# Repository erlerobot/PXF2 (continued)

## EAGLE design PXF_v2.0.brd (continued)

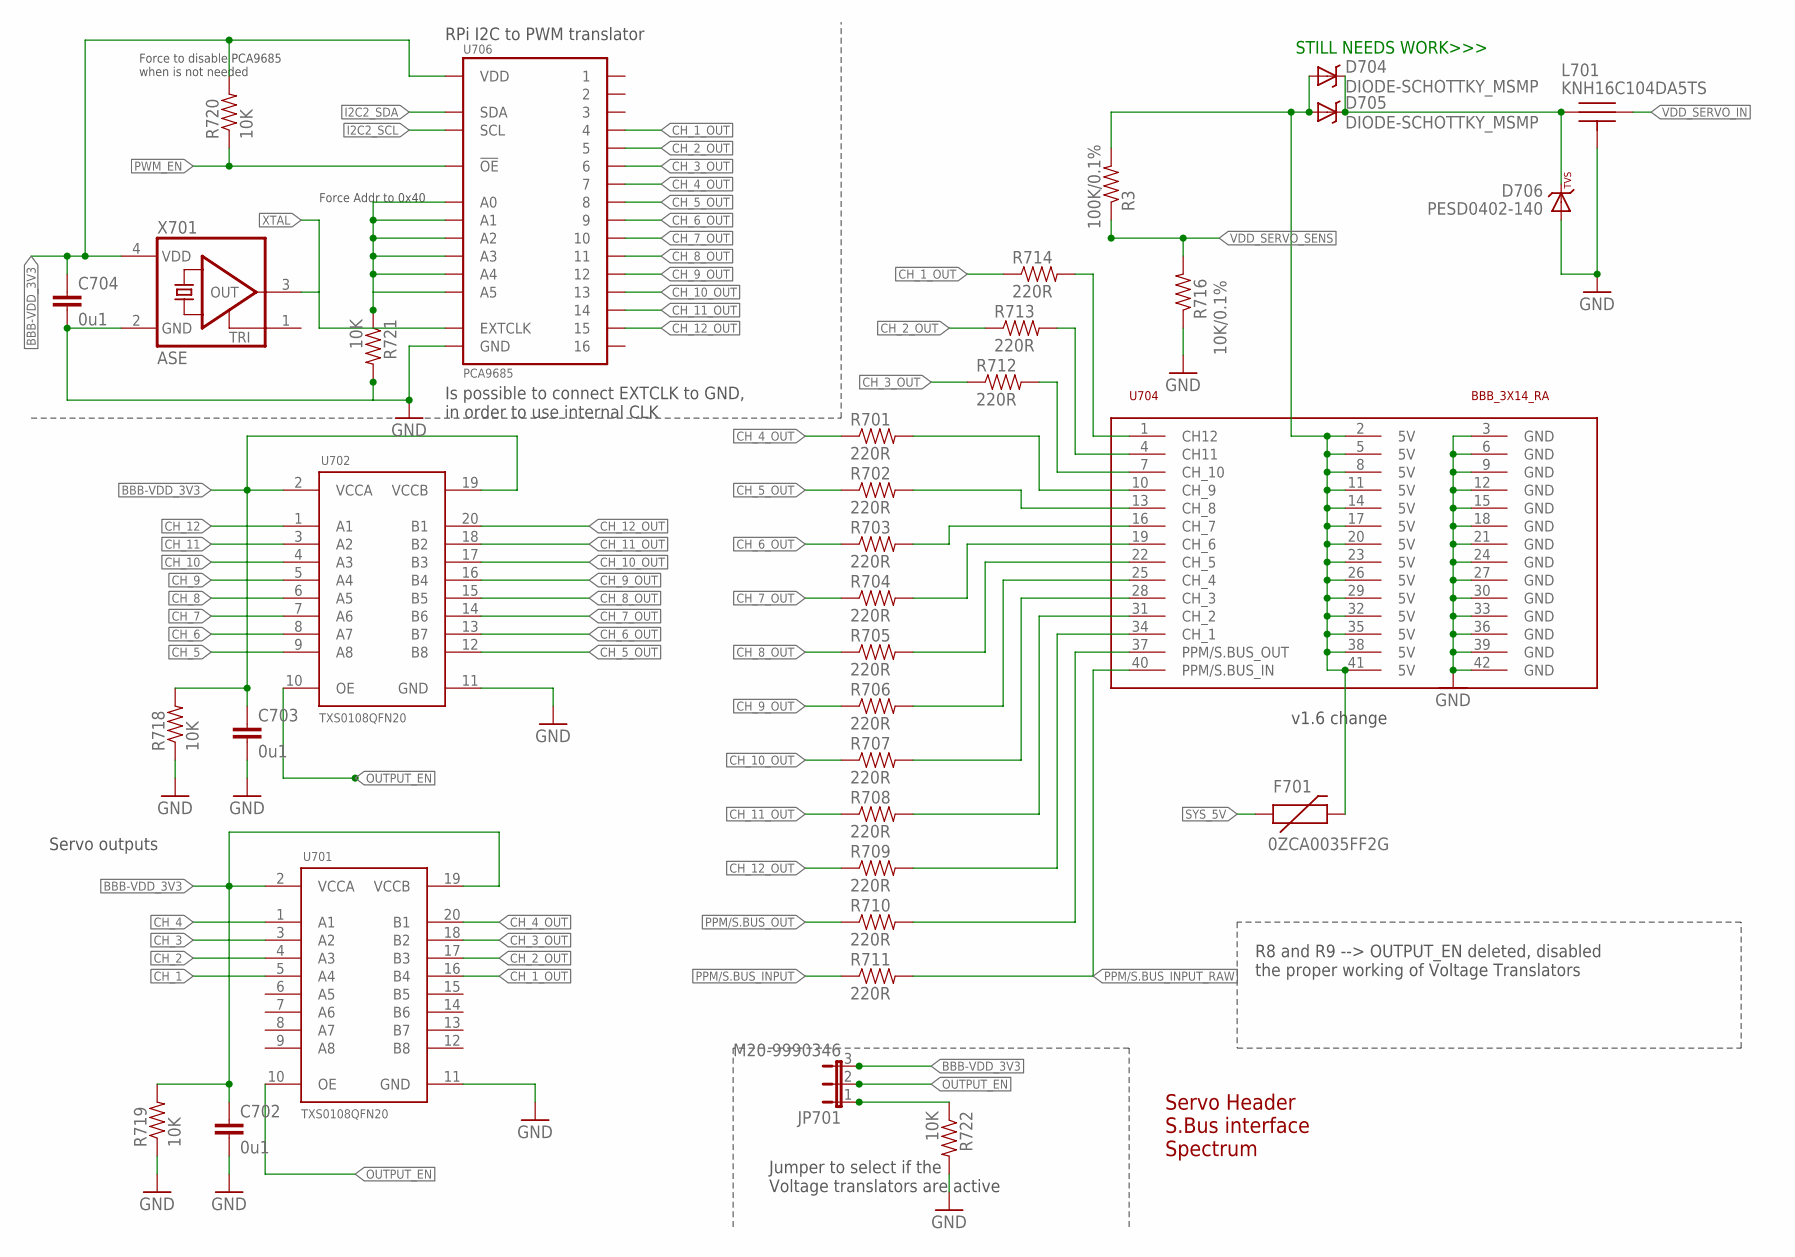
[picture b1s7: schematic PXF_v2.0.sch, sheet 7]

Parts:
C702, C703, C704: 0u1; 0402-CAP; PARTNO CC0402ZRY5V7BB104
D704, D705: DIODE-SCHOTTKY_MSMP; MICROSMP; PARTNO SS14
D706: PESD0402-140; 0402-TVS; PARTNO PESD0402-140
F701: 0ZCA0035FF2G; PTC-1206; PARTNO 0ZCA0035FF2G
JP701: M20-9990346; JP2
L701: KNH16C104DA5TS; KYOCERA-KNH16-DA; PARTNO KNH16C104DA5TS
R3: 100K/0.1%; 0402-RES; PARTNO ERA-2AEB104X
R701, R702, R703, R704, R705, R706, R707, R708, R709, R710, R711, R712, R713, R714: 220R; 0402-RES; PARTNO RC0402FR-07120RL
R716: 10K/0.1%; 0402-RES; PARTNO ERA-2AEB103X
R718, R719, R720, R721, R722: 10K; 0402-RES; PARTNO ERA-2AEB103X
U701, U702: TXS0108QFN20; QFN20-RGY; PARTNO TXS0108ERGYR
U704: BBB_3X14_RA; 3X14RA; PARTNO 07579
U706: PCA9685; HVQFN28
X701: ASE; MPN ASFL1-24.576MHZ-EC-T

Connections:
BBB-VDD_3V3: C702.P$1 (1), C703.P$1 (1), C704.P$1 (1), JP701.3, R718.P$2 (2), R719.P$2 (2), R720.P$2 (2), U701.2 (VCCA), U701.19 (VCCB), U702.2 (VCCA), U702.19 (VCCB), U706.25 (VDD), X701.4 (VDD); also elsewhere on the board
CH_1: U701.5 (A4); also elsewhere on the board
CH_1_OUT: R714.P$1 (1), U701.16 (B4), U706.6 (4)
CH_2: U701.4 (A3); also elsewhere on the board
CH_2_OUT: R713.P$1 (1), U701.17 (B3), U706.7 (5)
CH_3: U701.3 (A2); also elsewhere on the board
CH_3_OUT: R712.P$1 (1), U701.18 (B2), U706.8 (6)
CH_4: U701.1 (A1); also elsewhere on the board
CH_4_OUT: R701.P$1 (1), U701.20 (B1), U706.9 (7)
CH_5: U702.9 (A8); also elsewhere on the board
CH_5_OUT: R702.P$1 (1), U702.12 (B8), U706.10 (8)
CH_6: U702.8 (A7); also elsewhere on the board
CH_6_OUT: R703.P$1 (1), U702.13 (B7), U706.12 (9)
CH_7: U702.7 (A6); also elsewhere on the board
CH_7_OUT: R704.P$1 (1), U702.14 (B6), U706.13 (10)
CH_8: U702.6 (A5); also elsewhere on the board
CH_8_OUT: R705.P$1 (1), U702.15 (B5), U706.14 (11)
CH_9: U702.5 (A4); also elsewhere on the board
CH_9_OUT: R706.P$1 (1), U702.16 (B4), U706.15 (12)
CH_10: U702.4 (A3); also elsewhere on the board
CH_10_OUT: R707.P$1 (1), U702.17 (B3), U706.16 (13)
CH_11: U702.3 (A2); also elsewhere on the board
CH_11_OUT: R708.P$1 (1), U702.18 (B2), U706.17 (14)
CH_12: U702.1 (A1); also elsewhere on the board
CH_12_OUT: R709.P$1 (1), U702.20 (B1), U706.18 (15)
FMU-CH6-PROT: R708.P$2 (2), U704.31 (CH_2)
GND: C702.P$2 (2), C703.P$2 (2), C704.P$2 (2), D706.A, L701.P$3, L701.P$4, L701.P$5, R716.P$1 (1), R718.P$1 (1), R719.P$1 (1), R721.P$2 (2), R722.P$2 (2), U701.11 (GND), U702.11 (GND), U704.3 (GND), U704.6 (GND), U704.9 (GND), U704.12 (GND), U704.15 (GND), U704.18 (GND), U704.21 (GND), U704.24 (GND), U704.27 (GND), U704.30 (GND), U704.33 (GND), U704.36 (GND), U704.39 (GND), U704.42 (GND), U706.11 (GND), U706.PAD (GND), X701.2 (GND); also elsewhere on the board
I2C2_SCL: U706.23 (SCL); also elsewhere on the board
I2C2_SDA: U706.24 (SDA); also elsewhere on the board
IO-CH1-PROT: R707.P$2 (2), U704.28 (CH_3)
IO-CH8-PROT: R712.P$2 (2), U704.7 (CH_10)
unnamed: R721.P$1 (1), U706.1 (A3), U706.2 (A4), U706.21 (A5), U706.26 (A0), U706.27 (A1), U706.28 (A2)
unnamed: D704.CATHODE (C), D705.CATHODE (C), D706.C, L701.P$1
unnamed: JP701.1, R722.P$1 (1)
unnamed: D704.ANODE (A), D705.ANODE (A), F701.2, R3.P$2 (2), U704.2 (5V), U704.5 (5V), U704.8 (5V), U704.11 (5V), U704.14 (5V), U704.17 (5V), U704.20 (5V), U704.23 (5V), U704.26 (5V), U704.29 (5V), U704.32 (5V), U704.35 (5V), U704.38 (5V), U704.41 (5V)
unnamed: R701.P$2 (2), U704.10 (CH_9)
unnamed: R709.P$2 (2), U704.34 (CH_1)
unnamed: R702.P$2 (2), U704.13 (CH_8)
unnamed: R703.P$2 (2), U704.16 (CH_7)
unnamed: R704.P$2 (2), U704.19 (CH_6)
unnamed: R705.P$2 (2), U704.22 (CH_5)
unnamed: R706.P$2 (2), U704.25 (CH_4)
unnamed: R710.P$2 (2), U704.37 (PPM/S.BUS_OUT)
unnamed: R713.P$2 (2), U704.4 (CH11)
OUTPUT_EN: JP701.2, U701.10 (OE), U702.10 (OE); also elsewhere on the board
PPM-SBUS-PROT: R714.P$2 (2), U704.1 (CH12)
PPM/S.BUS_INPUT: R711.P$1 (1); also elsewhere on the board
PPM/S.BUS_INPUT_RAW: R711.P$2 (2), U704.40 (PPM/S.BUS_IN); also elsewhere on the board
PPM/S.BUS_OUT: R710.P$1 (1); also elsewhere on the board
PWM_EN: R720.P$1 (1), U706.20 (!OE); also elsewhere on the board
SYS_5V: F701.1; also elsewhere on the board
VDD_SERVO_IN: L701.P$2
VDD_SERVO_SENS: R3.P$1 (1), R716.P$2 (2); also elsewhere on the board
XTAL: U706.22 (EXTCLK), X701.3 (OUT); also elsewhere on the board

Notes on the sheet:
Servo Header S.Bus interface Spectrum
Servo outputs
STILL NEEDS WORK>>>
v1.6 change
R8 and R9 --> OUTPUT_EN deleted, disabled the proper working of Voltage Translators
RPi I2C to PWM translator
Force Addr to 0x40
Force to disable PCA9685 when is not needed
Jumper to select if the Voltage translators are active
Is possible to connect EXTCLK to GND, in order to use internal CLK

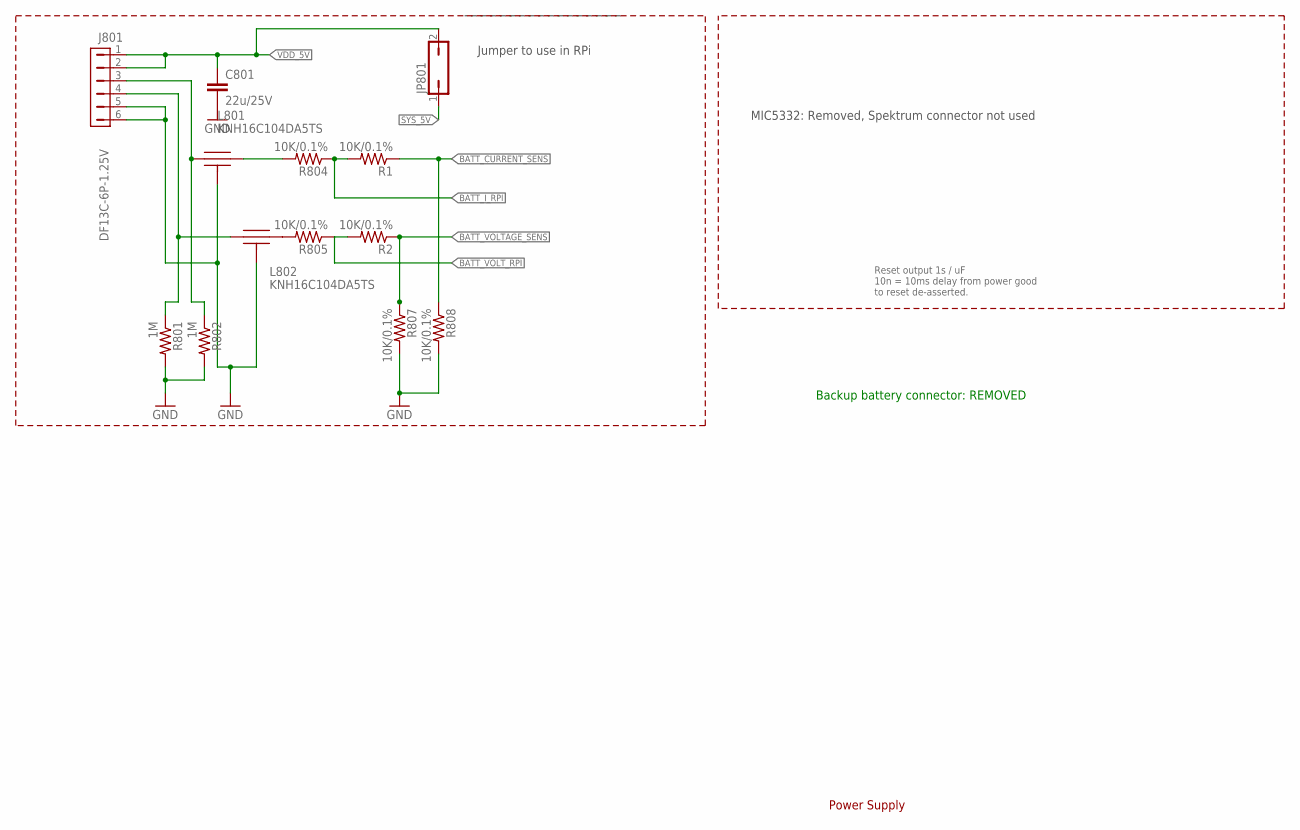
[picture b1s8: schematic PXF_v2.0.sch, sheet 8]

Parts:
C801: 22u/25V; 0805-CAP; PARTNO CL21A226MAQNNNE
J801: DF13C-6P-1.25V; PARTNO DF13C-6P-1.25V(20)
JP801: JP1Q; JP1; PARTNO 1-87215-0
L801, L802: KNH16C104DA5TS; KYOCERA-KNH16-DA; PARTNO KNH16C104DA5TS
R1, R2, R804, R805, R807, R808: 10K/0.1%; 0402-RES; PARTNO ERA-2AEB103X
R801, R802: 1M; 0402-RES; PARTNO RC0402FR-071ML

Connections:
BATT_CURRENT_SENS: R1.P$1 (1), R808.P$1 (1); also elsewhere on the board
BATT_CURRENT_SENS_PROT: J801.3, L801.P$1, R802.P$1 (1)
BATT_I_RPI: R1.P$2 (2), R804.P$1 (1); also elsewhere on the board
BATT_VOLTAGE_SENS: R2.P$1 (1), R807.P$1 (1); also elsewhere on the board
BATT_VOLTAGE_SENS_PROT: J801.4, L802.P$1, R801.P$1 (1); also elsewhere on the board
BATT_VOLT_RPI: R2.P$2 (2), R805.P$1 (1); also elsewhere on the board
GND: C801.P$2 (2), J801.5, J801.6, L801.P$3, L801.P$4, L801.P$5, L802.P$3, L802.P$4, L802.P$5, R801.P$2 (2), R802.P$2 (2), R807.P$2 (2), R808.P$2 (2); also elsewhere on the board
unnamed: L802.P$2, R805.P$2 (2)
unnamed: L801.P$2, R804.P$2 (2)
SYS_5V: JP801.1; also elsewhere on the board
VDD_5V: C801.P$1 (1), J801.1, J801.2, JP801.2; also elsewhere on the board

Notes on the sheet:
Power Supply
Reset output 1s / uF 10n = 10ms delay from power good to reset de-asserted.
Backup battery connector: REMOVED
MIC5332: Removed, Spektrum connector not used
Jumper to use in RPi

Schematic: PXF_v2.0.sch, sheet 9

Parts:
3V3_SENSORS: PAD.04; PAD.04X.04; PARTNO *
ADC_PR: PAD.04; PAD.04X.04; PARTNO *
BATT_I_RPI: PAD.04; PAD.04X.04; PARTNO *
BATT_VOLT_RPI: PAD.04; PAD.04X.04; PARTNO *
CAN_H: PAD.04; PAD.04X.04; PARTNO *
CAN_L: PAD.04; PAD.04X.04; PARTNO *
GND, GND.: PAD.04; PAD.04X.04; PARTNO *
JP901, JP902: FIDUCIAL1.5X3; FIDUCIAL-1.5X3; PARTNO *
OSHW_LOGO: OSHW-LOGOS; OSHW-LOGO-S; PARTNO *
OUTPUT_EN: PAD.04; PAD.04X.04; PARTNO *
PPM_INPUT: PAD.04; PAD.04X.04; PARTNO *
PPM_INPUT_BBB: PAD.04; PAD.04X.04; PARTNO *
PPM_INPUT_RAW: PAD.04; PAD.04X.04; PARTNO *
PPM_RPI: PAD.04; PAD.04X.04; PARTNO *
PWM_EN: PAD.04; PAD.04X.04; PARTNO *
RPI_5V_IN: PAD.04; PAD.04X.04; PARTNO *
S1RX, S1TX, S2RX, S2TX: PAD.04; PAD.04X.04; PARTNO *
VDD_3V3_BBB, VDD_5V_BRICK, VDD_5V_IN: PAD.04; PAD.04X.04; PARTNO *
VT_IN_1, VT_IN_2: PAD.04; PAD.04X.04; PARTNO *
VT_OUT_1, VT_OUT_2: PAD.04; PAD.04X.04; PARTNO *
XTAL: PAD.04; PAD.04X.04; PARTNO *

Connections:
BATT_I_RPI: BATT_I_RPI.P$1; also elsewhere on the board
BATT_VOLT_RPI: BATT_VOLT_RPI.P$1; also elsewhere on the board
BBB-VDD_3V3: VDD_3V3_BBB.P$1; also elsewhere on the board
CAN_H: CAN_H.P$1; also elsewhere on the board
CAN_L: CAN_L.P$1; also elsewhere on the board
GND: GND.P$1, GND..P$1; also elsewhere on the board
OUTPUT_EN: OUTPUT_EN.P$1; also elsewhere on the board
PPM/S.BUS_INPUT: PPM_INPUT.P$1, PPM_INPUT_BBB.P$1, PPM_RPI.P$1; also elsewhere on the board
PPM/S.BUS_INPUT_RAW: PPM_INPUT_RAW.P$1; also elsewhere on the board
PRESSURE_SENS_IN: ADC_PR.P$1; also elsewhere on the board
PWM_EN: PWM_EN.P$1; also elsewhere on the board
RPI_5V_IN: RPI_5V_IN.P$1; also elsewhere on the board
SYS_5V: VDD_5V_IN.P$1; also elsewhere on the board
TTYO4_RX: S1RX.P$1; also elsewhere on the board
TTYO4_TX: S1TX.P$1; also elsewhere on the board
TTYO5_RX: S2RX.P$1; also elsewhere on the board
TTYO5_TX: S2TX.P$1; also elsewhere on the board
VDD_3V3_SENSORS: 3V3_SENSORS.P$1; also elsewhere on the board
VDD_5V: VDD_5V_BRICK.P$1; also elsewhere on the board
VT_IN_1: VT_IN_1.P$1; also elsewhere on the board
VT_IN_2: VT_IN_2.P$1; also elsewhere on the board
VT_OUT_1: VT_OUT_1.P$1; also elsewhere on the board
VT_OUT_2: VT_OUT_2.P$1; also elsewhere on the board
XTAL: XTAL.P$1; also elsewhere on the board

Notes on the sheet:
Mounting holes to suit M3 fastener
and Richco R908 series spacer.
Use R908-5 spacers to stack with
other PX4 series boards (7.95 mm).
Production Testing Pads
Test and Fiducials
Minimum drill: 0.3 mm
Minimum trace width (use mm for traces): 0.15 mm
Minimum copper distance (all signals): 0.15 mm
Dimension / hole minimum distance: 0.2 mm
Layout grid: 4 mil, part grid: 4 mil. Dimensions / hole positions: 0.5 mm
Board: FR4 black, 1.0 mm. Solder stop on vias < 0.6 mm.
Signoff rules: Footprint checked, pinmap checked, schematic checked, cross-references to other pages checked.
Routing: 1: general/escape 2: ground 3: horizontal 4: vertical 5: power 6: general/escape
Fiducials for machine vision alignment.
Parts: Resistors: 0402 / 1% unless specified otherwise Capacitors: 0402 to 1206, ceramic, voltage rating: 10V unless specified

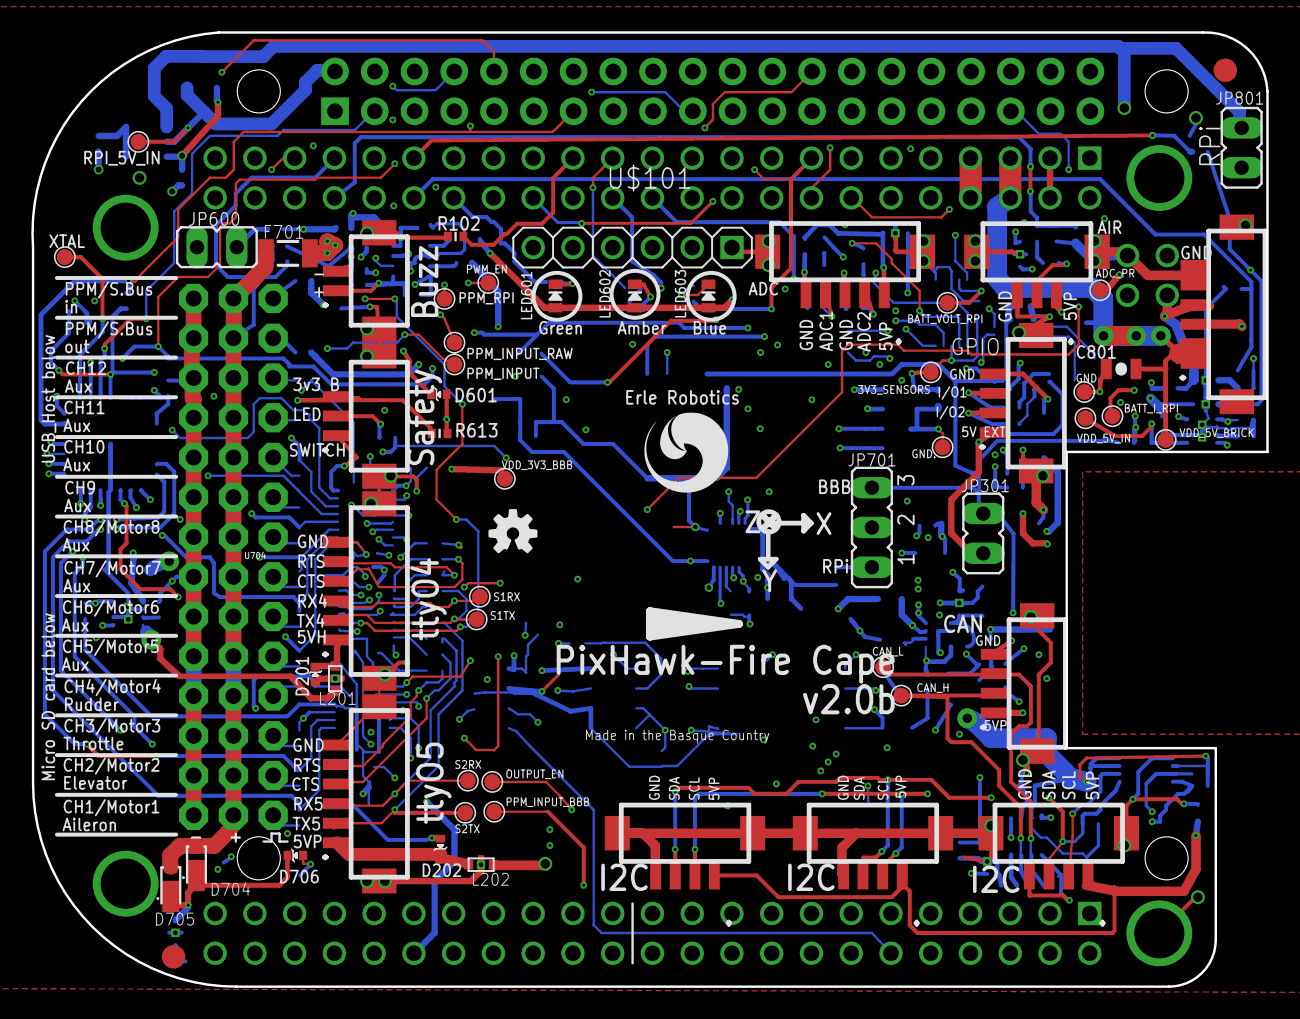
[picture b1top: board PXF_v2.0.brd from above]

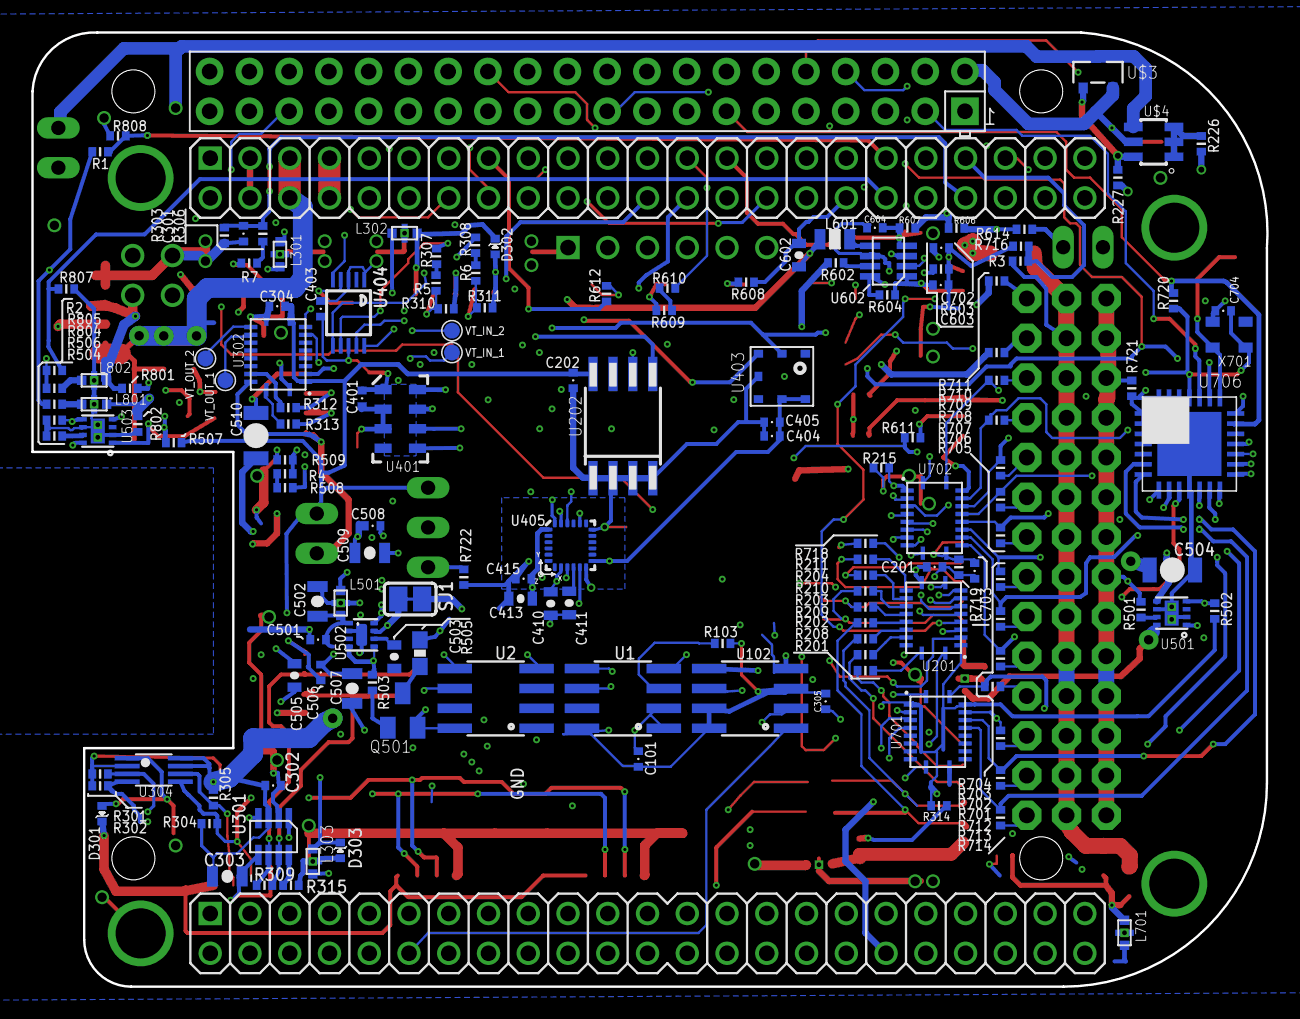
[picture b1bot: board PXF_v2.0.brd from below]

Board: 6 copper layers, 78.9 x 61.0 mm, 211 parts (151 on the bottom side), 166 nets.

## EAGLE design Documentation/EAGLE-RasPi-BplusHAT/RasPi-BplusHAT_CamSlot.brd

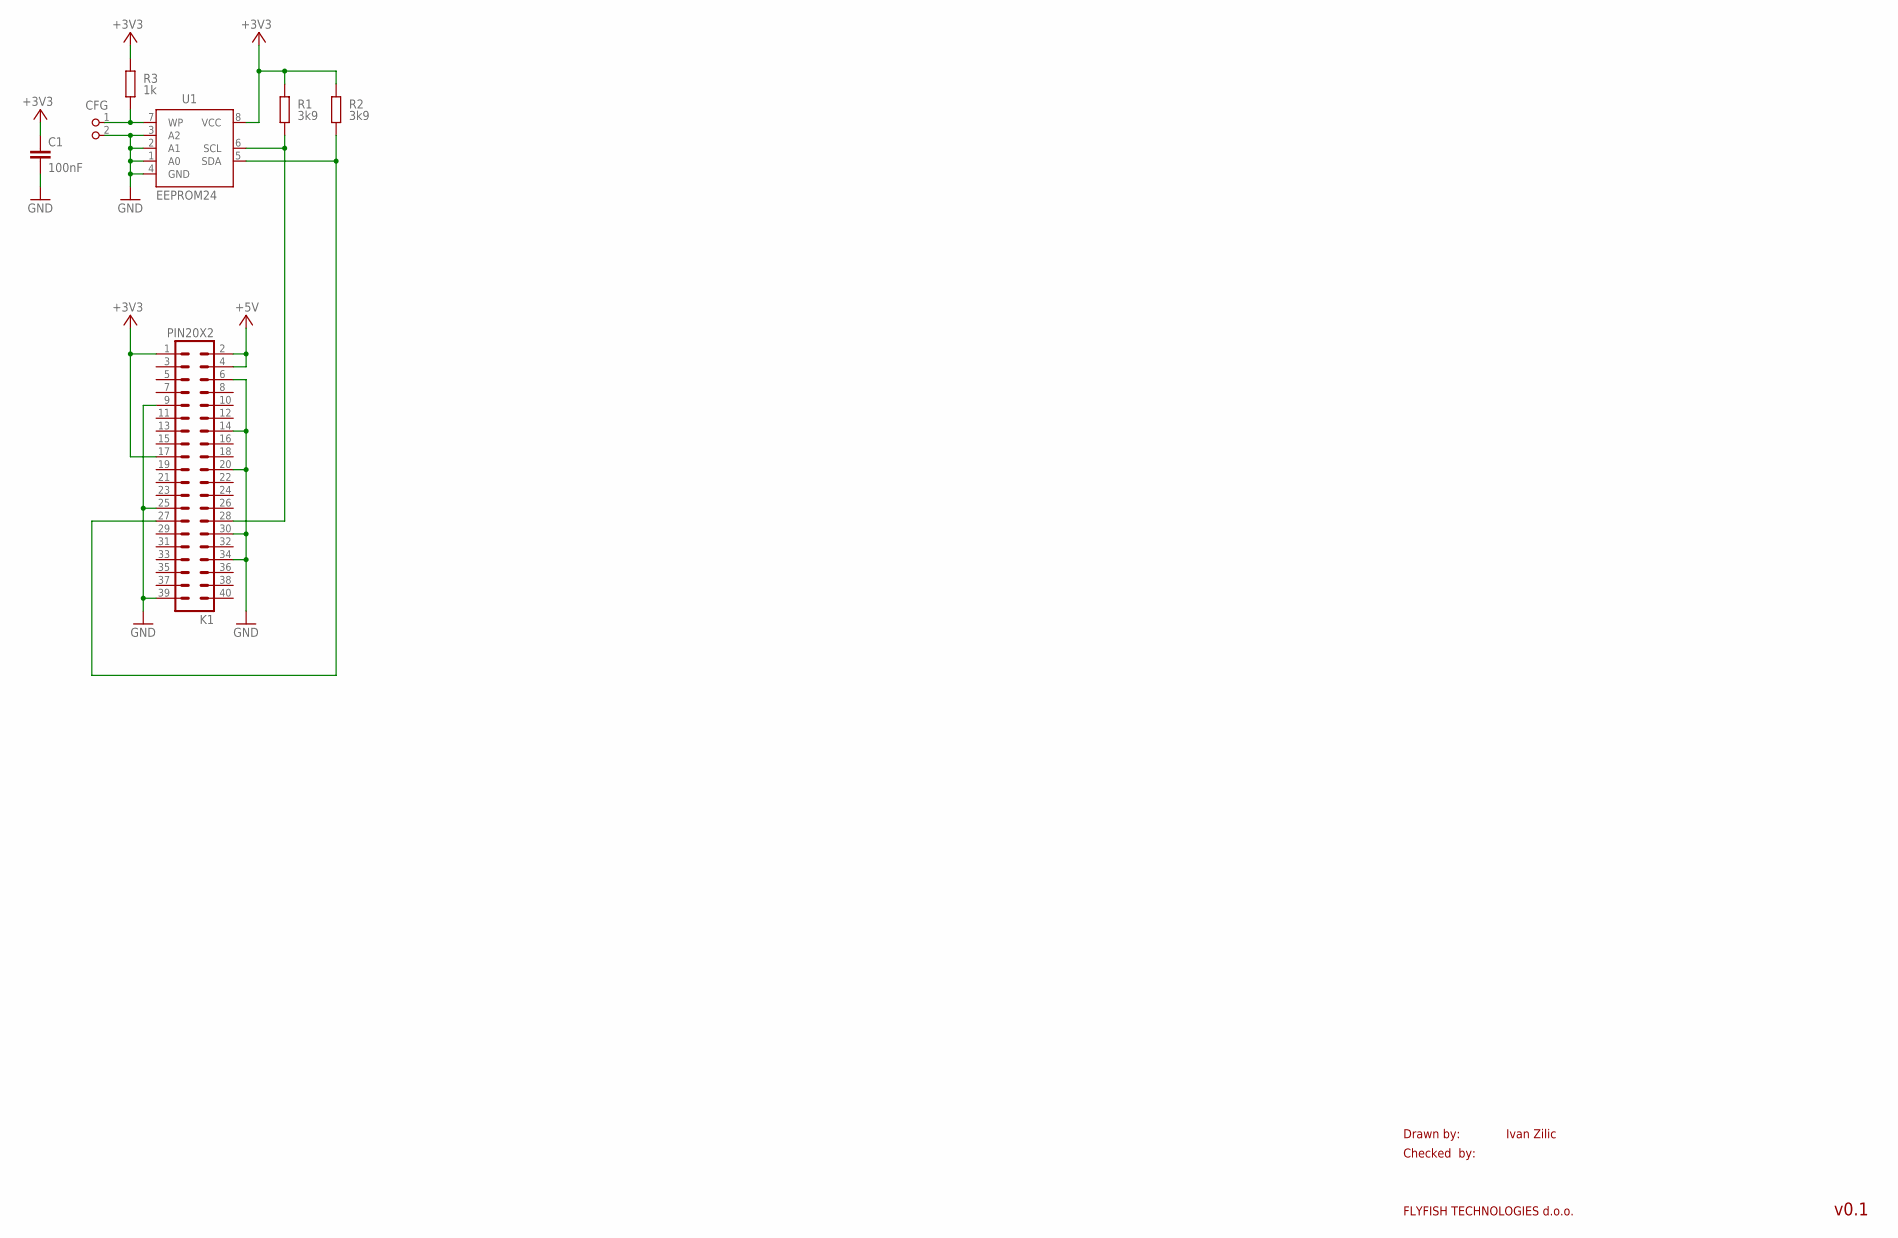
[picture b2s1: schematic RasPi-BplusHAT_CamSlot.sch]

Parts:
C1: 100nF; C0805K
CFG: PIN2_100; PIN_W_2
K1: PIN20X2; PIN_20X2
R1, R2: 3k9; M0805; TOLERANCE 5%
R3: 1k; M0805; TOLERANCE 5%
U1: EEPROM24; SOIC8

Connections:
+3V3: C1.1, K1.1, K1.17, R1.2, R2.2, R3.2, U1.8 (VCC)
+5V: K1.2, K1.4
GND: C1.2, CFG.2, K1.6, K1.9, K1.14, K1.20, K1.25, K1.30, K1.34, K1.39, U1.1 (A0), U1.2 (A1), U1.3 (A2), U1.4 (GND)
unnamed: K1.28, R1.1, U1.6 (SCL)
unnamed: K1.27, R2.1, U1.5 (SDA)
unnamed: CFG.1, R3.1, U1.7 (WP)

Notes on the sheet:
Drawn by:
Checked by:
FLYFISH TECHNOLOGIES d.o.o.
Ivan Zilic
v0.1

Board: 2 copper layers, 7 parts (0 on the bottom side), 6 nets, no tracks yet.
